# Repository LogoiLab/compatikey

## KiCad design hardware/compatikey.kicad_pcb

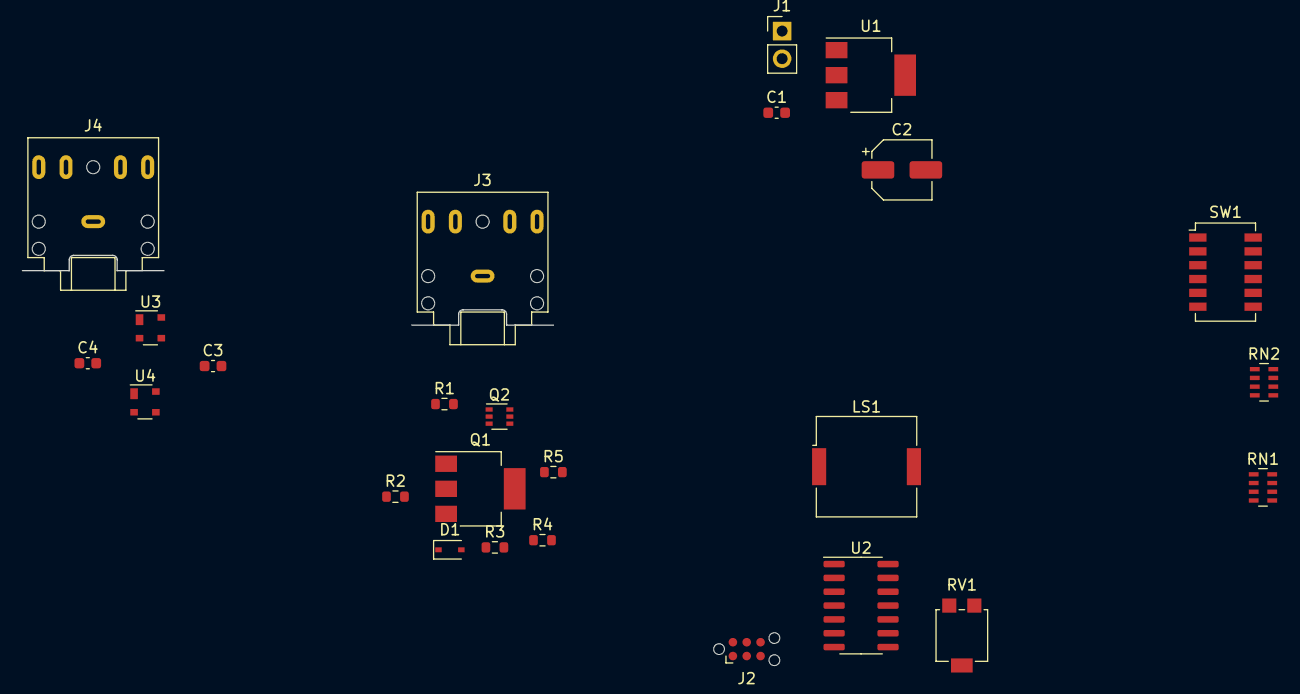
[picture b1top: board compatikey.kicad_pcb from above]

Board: 2 copper layers, 25 parts (0 on the bottom side), 32 nets, no tracks yet.

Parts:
C1: 1uF; C_0603_1608Metric
C2: 10uF; CP_Elec_5x3
C3, C4: 0.1uF; C_0603_1608Metric
D1: 1N4148WS; D_SOD-323
J1: Conn_01x02_Male; PinHeader_1x02_P2.54mm_Vertical
J2: TAG_Connect; Tag-Connect_TC2030-IDC-NL_2x03_P1.27mm_Vertical
J3, J4: AudioJack3; Jack_3.5mm_CUI_SJ1-3525N_Horizontal
LS1: Speaker; Buzzer_Murata_PKMCS0909E
Q1: PZT2222A; SOT-223-3_TabPin2
Q2: UM6K31N; SOT-363_SC-70-6
R1, R5: 10k; R_0603_1608Metric
R2, R3, R4: 300; R_0603_1608Metric
RN1: 10k; R_Array_Concave_4x0603
RN2: 20k; R_Array_Concave_4x0603
RV1: 20k; Potentiometer_Bourns_3314G_Vertical
SW1: Copal_CHS-06A; SW_DIP_SPSTx06_Slide_Copal_CHS-06A_W5.08mm_P1.27mm_JPin
U1: LD1117S50TR_SOT223; SOT-223-3_TabPin2
U2: ATtiny20-SS; SOIC-14_3.9x8.7mm_P1.27mm
U3, U4: MAX6816; SOT-143

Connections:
+5V: C1.1, C3.1, C4.1, R1.1, RV1.1, SW1.7, SW1.8, SW1.9, SW1.10, SW1.11, SW1.12, U1.2 (VO), U2.1 (VCC), U3.4 (VCC), U4.4 (VCC)
DIP_SEL_A: RN2.7 (R6.2), U2.13 (PA0)
GND: C1.2, C2.2, C3.2, C4.2, J1.2, J4.S, LS1.2, Q2.1 (S), Q2.4 (S), R5.2, RN1.6 (R6.1), RV1.3, U1.1 (GND), U2.14 (GND), U3.1 (GND), U4.1 (GND)
KEY_DRIVE: R3.1, U2.9 (PA4)
KEY_PULLUP_EN: R2.1, R4.1, U2.8 (PA5)
unnamed: D1.1 (K), Q2.5 (G), R4.2, R5.1
unnamed: D1.2 (A), Q2.2 (G), R3.2
unnamed: J2.1, U2.4 (~RESET/PB3)
unnamed: J2.2, U2.5 (PB2)
unnamed: J2.3, U2.3 (PB1)
unnamed: J2.4, U2.2 (PB0)
unnamed: J2.5, U2.6 (PA7)
unnamed: J3.R, J3.S, Q2.3 (D)
unnamed: J3.T, Q1.3 (E), Q2.6 (D)
unnamed: J4.R, U4.2 (IN)
unnamed: J4.T, U3.2 (IN)
unnamed: Q1.1 (B), R2.2
unnamed: Q1.2 (C), R1.2
unnamed: RN1.1 (R1.1), RN2.8 (R5.2)
unnamed: RN1.4 (R4.1), RN1.8 (R5.2)
unnamed: RN1.5 (R5.1), RN1.7 (R6.2)
unnamed: RN2.1 (R1.1), SW1.6
unnamed: RN2.2 (R2.1), SW1.5
unnamed: RN2.3 (R3.1), SW1.4
unnamed: RN2.4 (R4.1), SW1.3
unnamed: RN2.5 (R5.1), SW1.2
unnamed: RN2.6 (R6.1), SW1.1
PADDLE_L_DB: U2.10 (PA3), U4.3 (OUT)
PADDLE_R_DB: U2.11 (PA2), U3.3 (OUT)
PIEZO: J2.6, LS1.1, U2.7 (PA6)
VCC: C2.1, J1.1, U1.3 (VI)
WPM_SEL_A: RV1.2, U2.12 (PA1)

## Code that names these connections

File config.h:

#ifndef __config__
#define __config__

#include <avr/io.h>

#define DIP_SEL_A PINA0
#define WPM_SEL_A PINA1
#define PADDLE_R_DB PINA2
#define PADDLE_L_DB PINA3
#define PADDLE_L_DB PINA3
#define KEY_DRIVE PINA4
#define KEY_PULLUP_EN PINA5
#define PEIZO PINA6

#endif

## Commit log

2022-09-04 added gitignore
2022-09-04 init
2022-09-04 added emacs tmp to gitignore
2022-09-04 cleaned up makefile
